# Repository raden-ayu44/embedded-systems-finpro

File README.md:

# Hand grip dynamometer

Design and documentation for a hand grip strength meter, made for an embedded system course project. Two aluminium plates are squeezed, a load cell between them measures the force, an HX711 digitizes it, and an ESP32 shows the result on a 16×2 I2C LCD and logs it over USB serial.

- Target range: 20 to 70 kgf.
- Parts: ESP32 DevKit V1, HX711 module, CZL 601 80 kg bending-beam load cell, 16×2 I2C LCD (5 V) with a BSS138 4-channel level shifter, push button, LED. Powered from USB only.
- Housing: two plain Al 6061-T6 plates (140 × 40 × 8 mm) with 3 mm PLA spacers, joined to the load cell with M6 × 25 stainless flange bolts. The cable sits in a notch in spacer A and is held by a zip tie. Drawings are generated from the parameter CSV (`housing-load-cell/gambar/generate_drawings.py`).
- Budget: maximum Rp300.000.

**Status (24 Oct. 2026):** breadboard prototype working.
- **Firmware:** steps 0-11 written and tested on the board (state machine, non-blocking HX711 reading, LED rule, fault handling, watchdog, logging with ACK), built with Arduino IDE core 3.3.11. **Frozen for the UTS**: bug fixes only.
- **Laptop logger:** `laptop/logger.py` works: it writes three daily CSV files (results, faults, grip traces), answers ACK/NAK, and reconnects after a USB unplug.
- **Hardware design:** KiCad schematic and PCB v1 done; electronics housing and grip housing designed (not yet built). Bench tests: ESP32 pins, load cell, LCD (I2C 0x27), HX711; unloaded noise σ ≈ 0.7 g.
- **Not yet done:** calibration (moved to the final project; force values use the nominal scale, uncalibrated), building the housings.

Documents are written in Indonesian.

## Mulai di sini untuk UTS

Urutan baca untuk memahami purwarupa UTS (firmware, logger, layar), dari nol:

1. `README.md` (berkas ini): gambaran dan status.
2. [`catatan-proyek-hgd.md`](catatan-proyek-hgd.md): **hanya** gambaran proyek (Bagian 1), tujuan dan spesifikasi target S1-S5 (Bagian 2), fungsi perangkat (Bagian 6), riwayat keputusan (Bagian 14), dan status (Bagian 15). Bagian lain (sumber, anggaran, risiko, audit) tidak diperlukan untuk UTS.
3. [`firmware/alur-program-hgd.md`](firmware/alur-program-hgd.md) **Bagian 1-13**: arsitektur, struktur data, konstanta, fungsi, state machine, HX711, logging, antarmuka, uji, build, memori. Bagian 15-17 adalah lampiran lama dari catatan proyek; Bagian 6 dan 10 yang berlaku bila berbeda.
4. [`firmware/teks-lcd-hgd.md`](firmware/teks-lcd-hgd.md): semua layar LCD persis seperti dicetak firmware.
5. Kode firmware di [`firmware/hgd/hgd/`](firmware/hgd/hgd/) (mulai dari `hgd.ino`, lalu `config.h`, `types.h`, `fsm.cpp`). Folder ini juga isi ZIP firmware UTS.
6. [`laptop/logger.py`](laptop/logger.py): pencatat di laptop (CSV, ACK/NAK).
7. [`laptop/panduan-menjalankan-hgd.md`](laptop/panduan-menjalankan-hgd.md): cara menjalankan dari nol di laptop mana pun (pasang, flash, logger, uji bench satu sesi, buka CSV, grafik genggaman).

**Tidak diperlukan untuk UTS:** `housing-load-cell/`, `housing-elektronik/`, `kalibrasi/` (kalibrasi dipindah ke proyek akhir), `sitasi/`, PDF datasheet di `datasheet/pdf/`, dan sketsa uji lama di `firmware/sketches/` (hanya untuk uji modul awal).

## Start here

[`catatan-proyek-hgd.md`](catatan-proyek-hgd.md) is the main project notes and the index to everything else: requirements, specification, BOM, risks, schedule, decisions and changelog.

## Folders

| Folder | Contents |
|---|---|
| [`firmware/`](firmware/) | `hgd/`: the main ESP32 firmware (PlatformIO project; the sketch folder `hgd/hgd/` also opens in Arduino IDE and is the firmware ZIP); `alur-program-hgd.md`: program flow for the ESP32 firmware and the laptop-side logger (data, constants, functions, state machine, logging, tests, build); `teks-lcd-hgd.md`: every LCD screen exactly as the firmware prints it; `protokol-uji-bench-hgd.md`: bench test procedure and results; `sketches/` holds the early test sketches (pin loopback, LCD, HX711, button and LED, and the combined bench test) |
| [`laptop/`](laptop/) | `logger.py`: laptop-side logger (Python 3 + pyserial): reads the ESP32 log lines over USB serial, writes the daily CSV files, replies ACK/NAK; `plot_grip.py` and `plot_session.py`: force-time graphs from the grip CSV, one per trial with the ref window zoomed, and the whole session in sequence and overlapped (pandas + matplotlib, laptop or Google Colab); `panduan-menjalankan-hgd.md`: step-by-step guide to install, flash, run the logger, do a one-session bench test and open the CSV files on any Windows laptop |
| [`pcb/`](pcb/) | `desain-pcb-hgd.md` (schematic and PCB design), `pcb_netlist.xlsx` (components with official part names, KiCad symbols and footprints, netlist), `gambar/` (placement drawing, SVG), and [`kicad/`](pcb/kicad/README.md), the hub for KiCad files |
| [`housing-load-cell/`](housing-load-cell/) | Grip housing design, assumptions (`asumsi.md`), drawings in `gambar/` (SVG), Fusion 360 parameters and instructions in `fusion/` |
| [`housing-elektronik/`](housing-elektronik/) | Electronics housing design (LCD on the lid, shrink compensation, print rules) and Fusion 360 parameters in `fusion/` |
| [`kalibrasi/`](kalibrasi/) | Calibration protocol, `hgd_perhitungan.xlsx` (mechanical and electrical calculations with formulas), dumbbell dimensions, calibration drawings in `gambar/` |
| [`pengukuran/`](pengukuran/) | `tabel-pengukuran-hgd.xlsx`: caliper measurements, one tab per component, with official numbers where a datasheet gives them; `e1-noise-hgd.xlsx`: load cell noise test data; `hasil-multimeter-hgd.md`: every multimeter reading in one place, by date; `protokol-arus-rail-hgd.md`: how to measure the current on each rail with one multimeter (results in `pcb/desain-pcb-hgd.md` §5.1), with the breadboard wiring drawing `gambar/wiring-breadboard-hgd.png` (Wokwi, picture only; source `wokwi/diagram.json`) |
| [`datasheet/`](datasheet/) | Datasheet notes and the checklist of values still to fill in; the datasheet PDFs are in `pdf/` |
| [`sitasi/`](sitasi/) | Book and paper notes, local citation codes and the IEEE reference list; the open-access papers are in `pdf/` |

Drawings are SVG and open in any browser.

## License

Shared as-is for reference. Rights to the datasheets and papers in the `pdf/` folders stay with their publishers and manufacturers.

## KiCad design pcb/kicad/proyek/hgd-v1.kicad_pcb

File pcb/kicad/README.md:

# KiCad: simbol dan footprint kustom (v7)
**Proyek akhir - embedded system**

Folder ini adalah pusat semua berkas yang berkaitan dengan KiCad untuk PCB hand grip dynamometer. Daftar komponen, nama part resmi, dan nama simbol/footprint tiap komponen ada di [../pcb_netlist.xlsx](../pcb_netlist.xlsx) (sheet Komponen dan Modul luar PCB); desain dan keputusannya di [../desain-pcb-hgd.md](../desain-pcb-hgd.md).

## Struktur folder

Folder dibuat saat berkasnya ada; yang belum ada ditandai "belum".

| Jalur | Isi | Status |
|---|---|---|
| `README.md` | Hub ini: daftar simbol dan footprint kustom, aturan penamaan, kaitan ke berkas lain | Ada |
| `simbol/hgd.kicad_sym` | Pustaka simbol kustom proyek | Belum |
| `footprint/hgd.pretty/` | Pustaka footprint kustom proyek (satu berkas `.kicad_mod` per footprint) | Belum |
| `3d/` | Model 3D (`.step`) yang dipakai footprint kustom | Belum |
| `proyek/` | Berkas proyek KiCad (`.kicad_pro`, `.kicad_sch`, `.kicad_pcb`) | Ada: `hgd-v1.kicad_pro` (12 Nov. 2026; folder keluaran Gerber `gerber/`, STEP `hgd-v1.step`; uji beda-pustaka diatur ignore); `hgd-v1.kicad_pcb` (12 Nov. 2026: garis silkscreen footprint dirapikan dan D2 digeser 0,52 mm; 26 Okt. 2026: tiga belokan 45° dan via dijauhkan dari tepi, posisi footprint tetap, 56 via jahit GND, silkscreen tiga baris di kedua sisi "Kelompok 01 / Digital Hand Grip / Dynamometer", stackup FR4 1,6 mm; model 3D DevKit tertanam di berkas, `kicad-embed://`, tanpa jalur lokal); `hgd-v1.kicad_sch` (judul "Digital Hand Grip Dynamometer", 19 Okt. 2026; D2/R2, 24 no-connect, `PWR_FLAG`; ERC 0 error); `hgd-v1.step` (model 3D rakitan dari papan utama 26 Okt. 2026, untuk Fusion; D2 belum di posisi 12 Nov.; tanpa dua soket 1x15 DevKit, yang tidak memengaruhi desain housing). Salinan verbatim `hgd-v1-verbatim.kicad_pcb` (17 Okt., hanya untuk menampilkan soket di 3D) dihapus 27 Okt. 2026 |
| `pdf/` | Keluaran PDF: skema, penempatan, lembar uji pas skala 1:1 | Sebagian: `skema-hgd-v1.pdf` (26 Okt. 2026) |
| `gerber/` | Keluaran produksi (Gerber, bor) | Belum: Gerber 12 Nov. 2026 disimpan di luar repo sampai papan disetujui |

Pustaka standar KiCad (Device, Connector_Generic, Switch, LED_THT, dan lainnya) dipakai apa adanya dan tidak disalin ke sini.

## Aturan penamaan

- Pustaka kustom bernama `HGD`; simbol dipanggil `HGD:NamaSimbol`, footprint `HGD:NamaFootprint`.
- Nama simbol dan footprint mengikuti nama part resmi di datasheet bila ada (sama persis dengan kolom "Nama part resmi" di netlist).
- Tiap simbol dan footprint kustom diberi kolom `Datasheet` yang menunjuk ke berkas di `datasheet/pdf/` atau kode DS-* di `datasheet/datasheet-library.md`.

## Simbol dan footprint kustom yang direncanakan

Proyek KiCad `hgd-v1` memakai simbol dan footprint DevKit dari SnapEDA ("ESP32-DEVKIT-V1" oleh "Do it"; diunduh dari snapeda.com), sedangkan modul lain diwakili soket standar J1-J4. Simbol kustom di bawah tetap opsional.

| Nama | Jenis | Untuk | Keterangan | Sumber ukuran | Status |
|---|---|---|---|---|---|
| `HGD:ESP32_DevKit_V1_30pin` | Simbol | ESP32 DevKit V1 | Dua baris 15 pin, nama pin sesuai cetakan papan (EN, D18, D19, D21, D22, D25, D27, VIN, 3V3, GND, dan lainnya) | `datasheet/datasheet-library.md` (DS-ESP2, posisi pin) | Tidak perlu: dipakai simbol SnapEDA `ESP32-DEVKIT-V1` (U2) |
| `HGD:ESP32_DevKit_V1_Outline` | Footprint | Kontur papan di PCB pembawa | 51,5 x 28,2 mm, dua baris soket 15 pin jarak 25,4 mm (hasil ukur 25,3), area antena bebas tembaga | Tab ESP32 di [../../pengukuran/tabel-pengukuran-hgd.xlsx](../../pengukuran/tabel-pengukuran-hgd.xlsx) | Tidak perlu: dipakai footprint SnapEDA `MODULE_ESP32_DEVKIT_V1` (diperiksa: pitch 2,54, baris 25,4, bor 1,02, pad 1 = 3V3, pad 16 = EN; lubang NPTH bawaan dihapus) |
| `HGD:HX711_Module_XFW` | Simbol | Modul HX711 | Sisi sinyal GND, DT, SCK, VCC; sisi load cell E+, E-, A-, A+, B-, B+ | DS-HX1 | Belum |
| `HGD:LCD1602_I2C_Backpack` | Simbol | LCD dengan backpack | GND, VCC, SDA, SCL | DS-LCD1, DS-I2C1 | Belum |

## Pemeriksaan sebelum memakai nama dari netlist

- Nama pustaka standar di `pcb_netlist.xlsx` ditulis dari pustaka KiCad yang umum; cocokkan dengan yang benar-benar ada di instalasi Anda (nama bisa berbeda antar versi KiCad).
- Skema KiCad `hgd-v1` sudah diperiksa (15 Okt. 2026): netlist benar, termasuk kedua GND DevKit. Pembersihan berkas PCB sebelum gerber ada di Bagian 8.3 [../desain-pcb-hgd.md](../desain-pcb-hgd.md).
- **Skema dan PCB v1 selesai (17 Okt. 2026; versi akhir 26 Okt. 2026; revisi 12 Nov. 2026), belum disetujui.** Di `proyek/`: `hgd-v1.kicad_pro`, `hgd-v1.kicad_sch` (ERC 0 error), `hgd-v1.kicad_pcb` (DRC 0 error, tanpa pengecualian; paritas skema-PCB 0 beda), `hgd-v1.step` (26 Okt. 2026). Gerber v1 diekspor ulang 12 Nov. 2026 dan dicek di JLCDFM, disimpan di luar repo sampai disetujui. Setelan KiCad langkah demi langkah: Bagian 8.5 [../desain-pcb-hgd.md](../desain-pcb-hgd.md). Daftar Assign Footprints: Bagian 8.1a [../desain-pcb-hgd.md](../desain-pcb-hgd.md). Langkah kerja: [../log-kerja-kicad-hgd.md](../log-kerja-kicad-hgd.md).

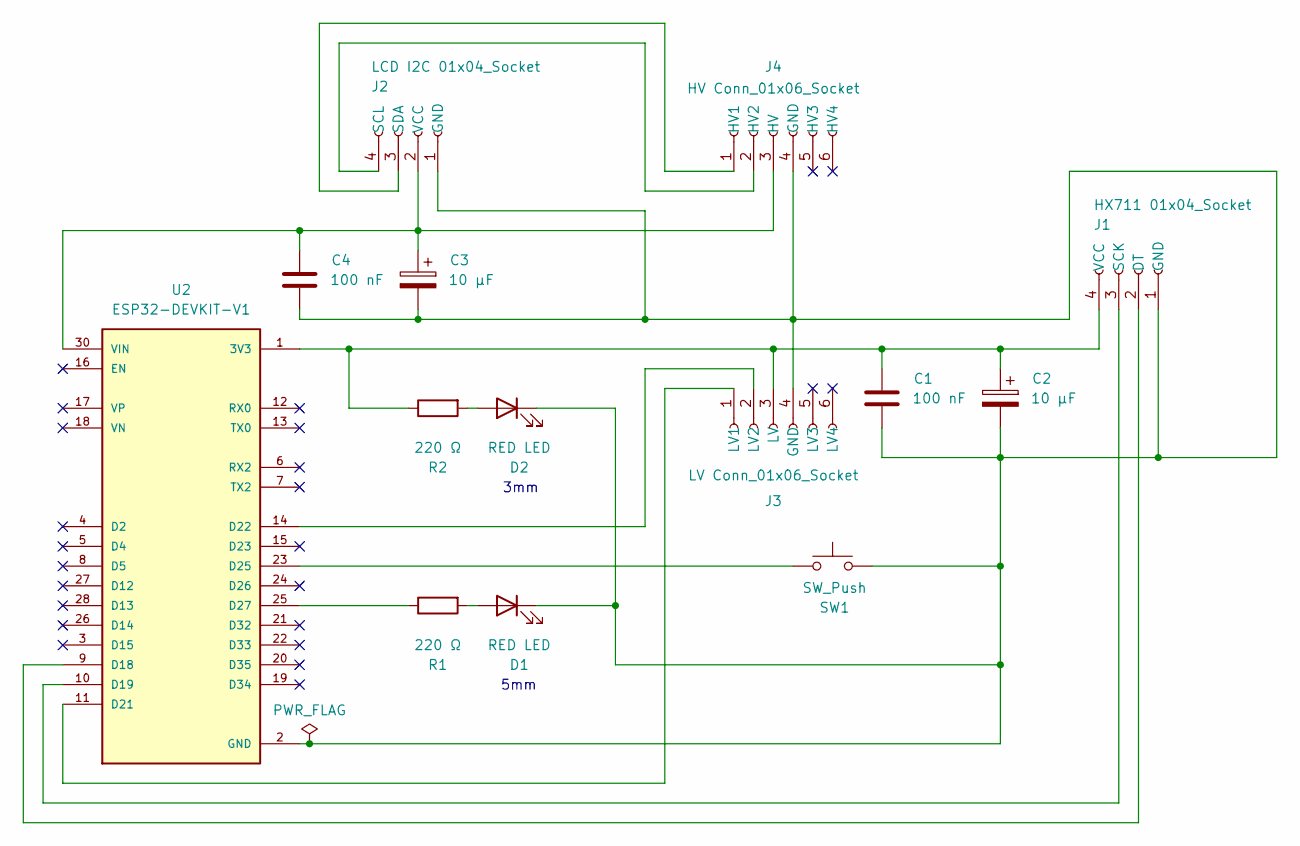
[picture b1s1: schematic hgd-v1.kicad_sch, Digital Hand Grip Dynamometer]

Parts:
C1, C4: 100 nF; C_Disc_D7.0mm_W2.5mm_P5.00mm
C2, C3: 10 µF; CP_Radial_D5.0mm_P2.50mm
D1: RED LED; LED_D5.0mm
D2: RED LED; LED_D3.0mm
J1: HX711 01x04_Socket; PinSocket_1x04_P2.54mm_Vertical
J2: LCD I2C 01x04_Socket; PinSocket_1x04_P2.54mm_Vertical
J3: LV Conn_01x06_Socket; PinSocket_1x06_P2.54mm_Vertical
J4: HV Conn_01x06_Socket; PinSocket_1x06_P2.54mm_Vertical
R1, R2: 220 Ω; R_Axial_DIN0207_L6.3mm_D2.5mm_P10.16mm_Horizontal
SW1: SW_Push; SW_PUSH_6mm_H13mm
U2: ESP32-DEVKIT-V1; MODULE_ESP32_DEVKIT_V1; PARTREV N/A

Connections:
GND: C1.2, C2.2, C3.2, C4.2, D1.1 (K), D2.1 (K), J1.1 (GND), J2.1 (GND), J3.4 (GND), J4.4 (GND), SW1.2, U2.2 (GND), U2.29 (GND)
unnamed: D1.2 (A), R1.2
unnamed: D2.2 (A), R2.2
unnamed: J1.2 (DT), U2.9 (D18)
unnamed: J1.3 (SCK), U2.10 (D19)
unnamed: C1.1, C2.1, J1.4 (VCC), J3.3 (LV), R2.1, U2.1 (3V3)
unnamed: J2.4 (SCL), J4.2 (HV2)
unnamed: J2.3 (SDA), J4.1 (HV1)
unnamed: C3.1, C4.1, J2.2 (VCC), J4.3 (HV), U2.30 (VIN)
unnamed: J3.1 (LV1), U2.11 (D21)
unnamed: J3.2 (LV2), U2.14 (D22)
unnamed: SW1.1, U2.23 (D25)
unnamed: R1.1, U2.25 (D27)

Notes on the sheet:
3mm
5mm

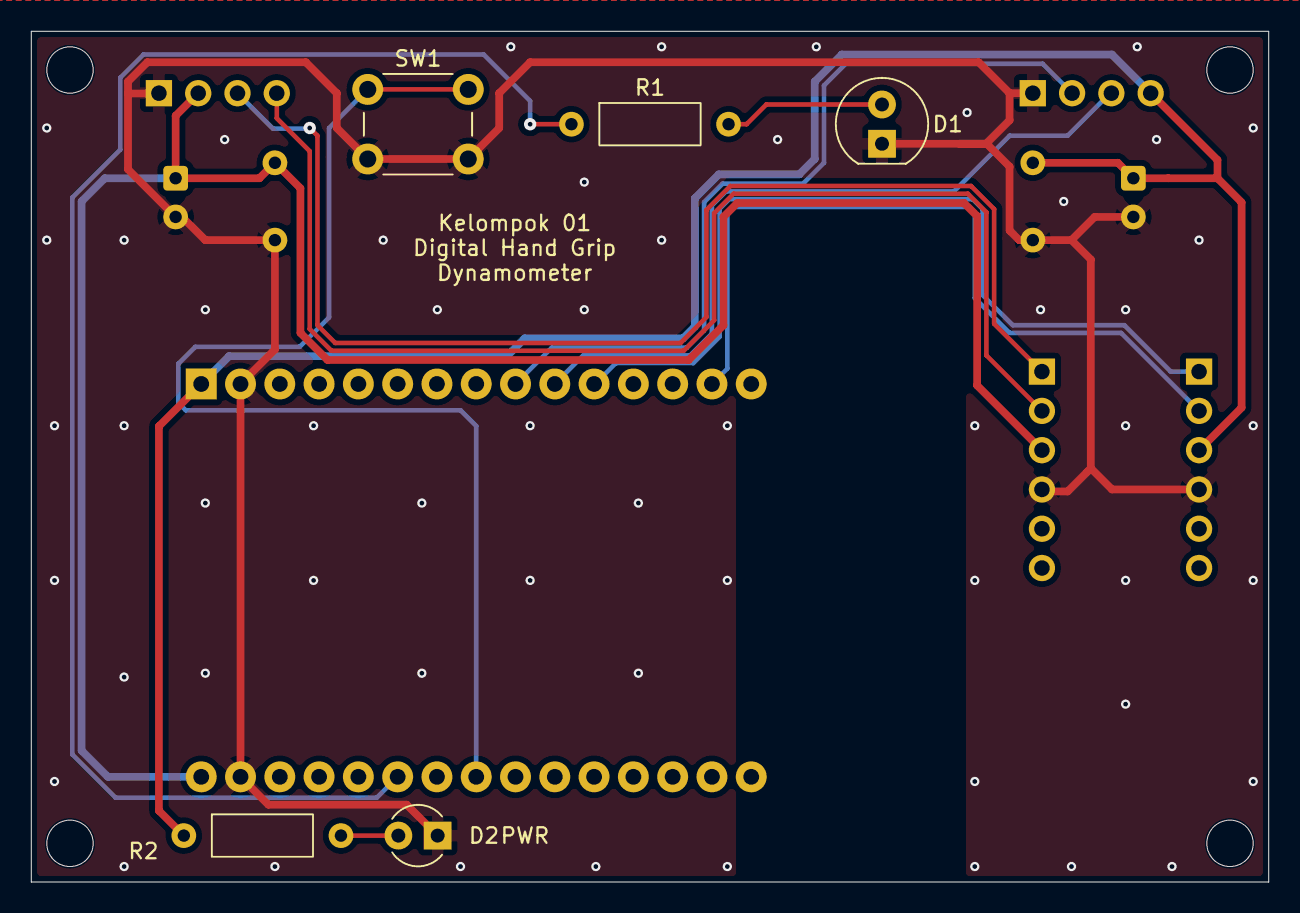
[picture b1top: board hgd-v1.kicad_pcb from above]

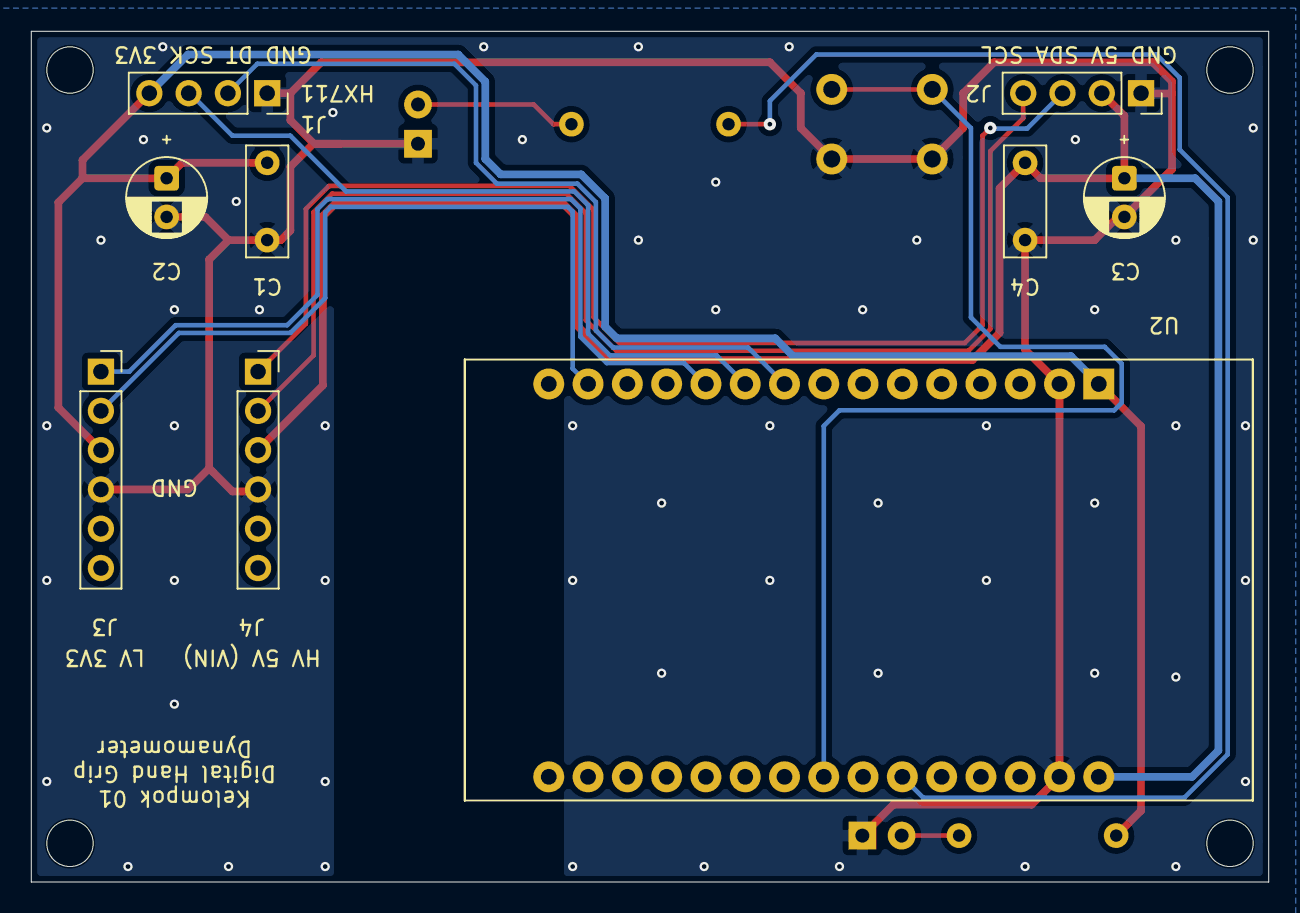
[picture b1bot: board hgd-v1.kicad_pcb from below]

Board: 2 copper layers, 80.0 x 55.0 mm, 18 parts (9 on the bottom side), 13 nets.

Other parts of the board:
H1, H2, H3, H4: MountingHole_3mm
